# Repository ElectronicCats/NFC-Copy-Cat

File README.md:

# NFC Copy Cat

NFC Copy Cat, manufactured by Electronic Cats, is a small device that combines two powerful cybersecurity tools, NFCopy and MagSpoof. NFCopy works by reading or emulating an NFC card; depending on the necessities of the researcher. On the other hand, MagSpoof can wirelessly emulate/spoof any magnetic stripe card. So using NFC Copy Cat, the user will have a device capable of storing magnetic stripe data or NFC payment data to be replayed later — known in the cybersecurity world as a replay attack. 

To show the capabilities of NFC Copy Cat, the emulation example will use a Visa MSD protocol. So be aware that this type of transaction will not be accepted in some payment systems.

NFC Copy Cat combines a simple user interface that can be programmed using Arduino IDE. Adding a micro USB connection, 3.7V LiPo battery connector, antenna, two programmable buttons, LEDs and a reset button. The most important part, NFC Copy Cat is an open hardware project. So anyone could modify or redesign it on their own.

Devices like NFC Copy Cat are essential for researchers, students, teachers or anyone interested in payment systems. It will help to understand how the payment system works, the communications or the APDU protocol. 

Some of the code examples that will be available introduce different concepts. For example, how to detect a card reader, how to detect an NFC card, how to use MagSpoof using a button as a trigger to spoof, how to use NFC with a button to emulate, how to read a Visa card, how to emulate a Visa MSD card, how to generate challenges to extract card information or how to combine both tools: NFCopy and MagSpoof.

## Features:
- Microcontroller SAMD21 ARM 32-bit Cortex M0
- Memory Flash for support Circuit Python
- Battery Charger 3.7v
- Compatible con Adafruit PN532 breakout
- Compatible con NFC Module V3

### Included Complete Version:
- NFC Copy Cat
- Coil for Magspoof
- NFC Module V3 +Tag 
### Included Single Version:
- NFC Copy Cat
- Coil for Magspoof

## Wiki and Getting Started
[Getting Started in our Wiki](https://github.com/ElectronicCats/NFC-Copy-Cat/wiki)

## Disclaimer
NFC Copy Cat is a wireless penetration testing tool intended solely for use in authorized security audits, where such usage is permitted by applicable laws and regulations. Before utilizing this tool, it is crucial to ensure compliance with all relevant legal requirements and obtain appropriate permissions from the relevant authorities.

It is essential to note that the board does not provide any means or authorization to utilize credit cards or engage in any financial transactions that are not legally authorized. Electronic Cats holds no responsibility for any unauthorized use of the tool or any resulting damages.

## License

Electronic Cats invests time and resources providing this open source design, please support Electronic Cats and open-source hardware by purchasing products from Electronic Cats!

Designed by Electronic Cats.

Firmware released under an GNU AGPL v3.0 license. See the LICENSE file for more information.

Hardware released under an CERN Open Hardware Licence v1.2. See the LICENSE_HARDWARE file for more information.

Electronic Cats is a registered trademark, please do not use if you sell these PCBs.

8 July 2019

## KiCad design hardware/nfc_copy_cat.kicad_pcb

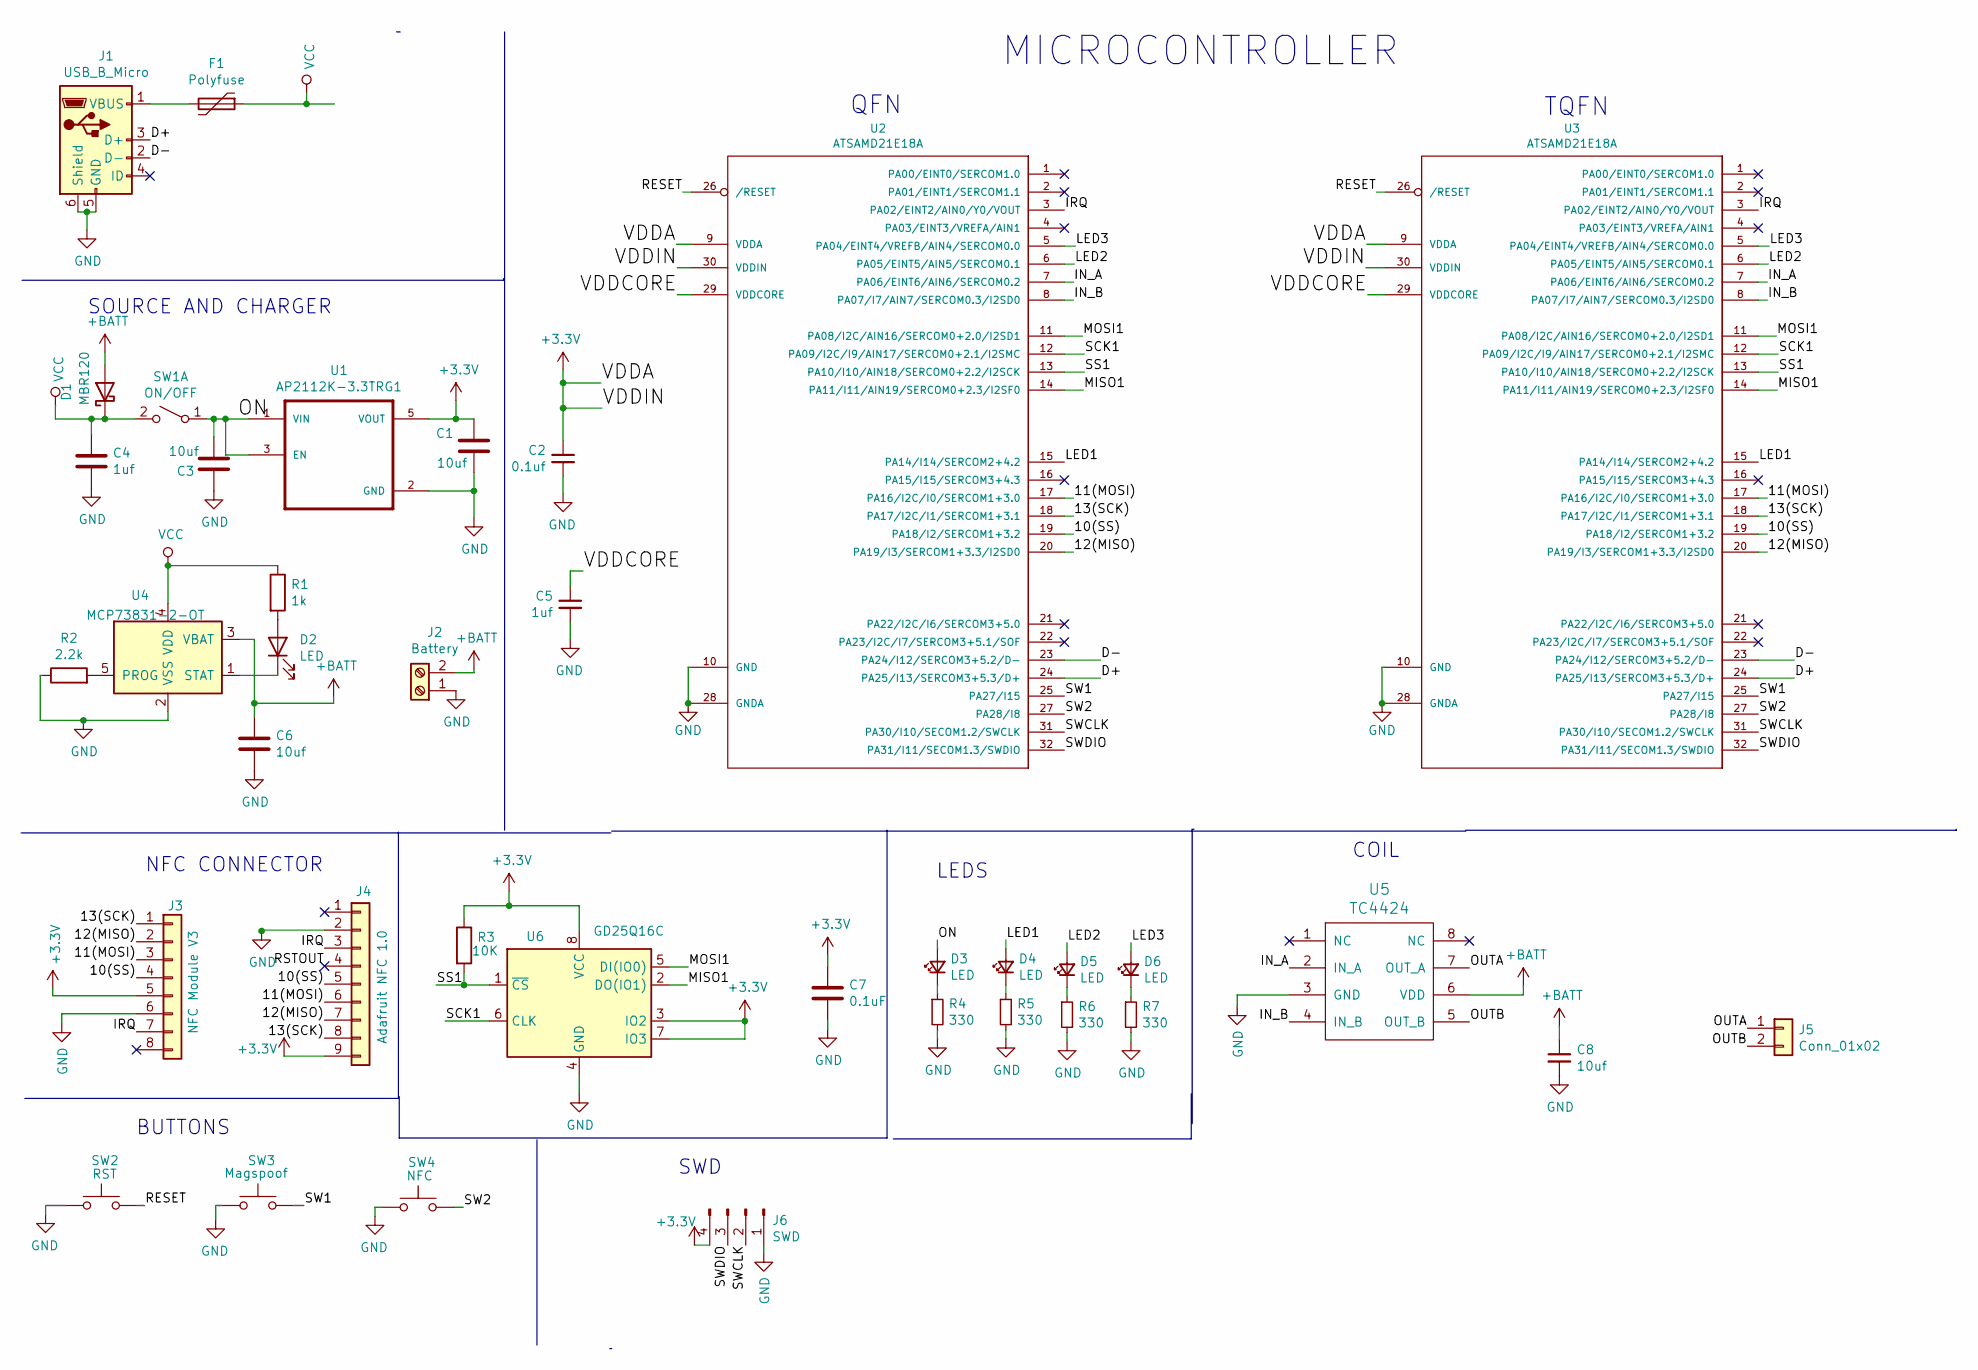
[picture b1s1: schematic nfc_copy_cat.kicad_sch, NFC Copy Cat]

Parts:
C1, C3, C6, C8: 10uf; C_0805_2012Metric_Pad1.15x1.40mm_HandSolder
C2: 0.1uf; C_0805_2012Metric_Pad1.15x1.40mm_HandSolder
C4, C5: 1uf; C_0805_2012Metric_Pad1.15x1.40mm_HandSolder
C7: 0.1uF; C_0805_2012Metric_Pad1.15x1.40mm_HandSolder
D1: MBR120; D_SOD-123
D2, D3, D4, D5, D6: LED; LED_0805_2012Metric_Pad1.15x1.40mm_HandSolder
F1: Polyfuse; Fuse_0805_2012Metric_Pad1.15x1.40mm_HandSolder
J1: USB_B_Micro; U254051N4BH806
J2: Battery; PinHeader_1x02_P2.54mm_Vertical
J3: NFC Module V3; PinHeader_1x08_P2.54mm_Vertical
J4: Adafruit NFC 1.0; PinHeader_1x09_P2.54mm_Vertical
J5: Conn_01x02; PinHeader_1x02_P2.54mm_Vertical
J6: SWD; PinHeader_1x04_P2.54mm_Vertical
R1: 1k; R_0805_2012Metric
R2: 2.2k; R_0805_2012Metric_Pad1.15x1.40mm_HandSolder
R3: 10K; R_0805_2012Metric_Pad1.15x1.40mm_HandSolder
R4: 330; R_0805_2012Metric
R5, R6, R7: 330; R_0805_2012Metric_Pad1.15x1.40mm_HandSolder
SW1: ON/OFF; Micro_interruptor_SPDT
SW2: RST; SW_SPST_TL3342
SW3: Magspoof; SW_SPST_TL3342
SW4: NFC; SW_SPST_TL3342
U1: AP2112K-3.3TRG1; SOT-23-5_HandSoldering
U2: ATSAMD21E18A; QFN-32-1EP_5x5mm_P0.5mm_EP3.6x3.6mm
U3: ATSAMD21E18A; TQFP-32_7x7mm_P0.8mm
U4: MCP73831-2-OT; SOT-23-5
U5: TC4424; SOIC-8_3.9x4.9mm_P1.27mm
U6: GD25Q16C; SOIC-8_5.23x5.23mm_P1.27mm

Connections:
+3V3: C1.1, C2.1, C7.1, J3.5, J4.9, J6.4, R3.1, U1.5 (VOUT), U2.9 (VDDA), U2.30 (VDDIN), U3.9 (VDDA), U3.30 (VDDIN), U6.3 (IO2), U6.7 (IO3), U6.8 (VCC)
+BATT: C6.1, C8.1, D1.2 (A), J2.2, U4.3 (VBAT), U5.6 (VDD)
/10(SS): J3.4, J4.5, U2.19 (PA18/I2/SERCOM1+3.2), U3.19 (PA18/I2/SERCOM1+3.2)
/11(MOSI): J3.3, J4.6, U2.17 (PA16/I2C/I0/SERCOM1+3.0), U3.17 (PA16/I2C/I0/SERCOM1+3.0)
/12(MISO): J3.2, J4.7, U2.20 (PA19/I3/SERCOM1+3.3/I2SD0), U3.20 (PA19/I3/SERCOM1+3.3/I2SD0)
/13(SCK): J3.1, J4.8, U2.18 (PA17/I2C/I1/SERCOM1+3.1), U3.18 (PA17/I2C/I1/SERCOM1+3.1)
/D+: J1.3 (D+), U2.24 (PA25/I13/SERCOM3+5.3/D+), U3.24 (PA25/I13/SERCOM3+5.3/D+)
/D-: J1.2 (D-), U2.23 (PA24/I12/SERCOM3+5.2/D-), U3.23 (PA24/I12/SERCOM3+5.2/D-)
/IN_A: U2.7 (PA06/EINT6/AIN6/SERCOM0.2), U3.7 (PA06/EINT6/AIN6/SERCOM0.2), U5.2 (IN_A)
/IN_B: U2.8 (PA07/I7/AIN7/SERCOM0.3/I2SD0), U3.8 (PA07/I7/AIN7/SERCOM0.3/I2SD0), U5.4 (IN_B)
/IRQ: J3.7, J4.3, U2.3 (PA02/EINT2/AIN0/Y0/VOUT), U3.3 (PA02/EINT2/AIN0/Y0/VOUT)
/LED1: D4.2 (A), U2.15 (PA14/I14/SERCOM2+4.2), U3.15 (PA14/I14/SERCOM2+4.2)
/LED2: D5.2 (A), U2.6 (PA05/EINT5/AIN5/SERCOM0.1), U3.6 (PA05/EINT5/AIN5/SERCOM0.1)
/LED3: D6.2 (A), U2.5 (PA04/EINT4/VREFB/AIN4/SERCOM0.0), U3.5 (PA04/EINT4/VREFB/AIN4/SERCOM0.0)
/MISO1: U2.14 (PA11/I11/AIN19/SERCOM0+2.3/I2SF0), U3.14 (PA11/I11/AIN19/SERCOM0+2.3/I2SF0), U6.2 (DO(IO1))
/MOSI1: U2.11 (PA08/I2C/AIN16/SERCOM0+2.0/I2SD1), U3.11 (PA08/I2C/AIN16/SERCOM0+2.0/I2SD1), U6.5 (DI(IO0))
/OUTA: J5.1, U5.7 (OUT_A)
/OUTB: J5.2, U5.5 (OUT_B)
/RESET: SW2.2, U2.26 (/RESET), U3.26 (/RESET)
/RSTOUT: J4.4
/SCK1: U2.12 (PA09/I2C/I9/AIN17/SERCOM0+2.1/I2SMC), U3.12 (PA09/I2C/I9/AIN17/SERCOM0+2.1/I2SMC), U6.6 (CLK)
/SS1: R3.2, U2.13 (PA10/I10/AIN18/SERCOM0+2.2/I2SCK), U3.13 (PA10/I10/AIN18/SERCOM0+2.2/I2SCK), U6.1 (~CS)
/SW1: SW3.2, U2.25 (PA27/I15), U3.25 (PA27/I15)
/SW2: SW4.2, U2.27 (PA28/I8), U3.27 (PA28/I8)
/SWCLK: J6.2, U2.31 (PA30/I10/SECOM1.2/SWCLK), U3.31 (PA30/I10/SECOM1.2/SWCLK)
/SWDIO: J6.3, U2.32 (PA31/I11/SECOM1.3/SWDIO), U3.32 (PA31/I11/SECOM1.3/SWDIO)
/VDDCORE: C5.1, U2.29 (VDDCORE), U3.29 (VDDCORE)
GND: C1.2, C2.2, C3.2, C4.2, C5.2, C6.2, C7.2, C8.2, J1.5 (GND), J1.6 (Shield), J2.1, J3.6, J4.2, J6.1, R2.1, R4.2, R5.2, R6.2, R7.2, SW2.1, SW3.1, SW4.1, U1.2 (GND), U2.10 (GND), U2.28 (GNDA), U3.10 (GND), U3.28 (GNDA), U4.2 (VSS), U5.3 (GND), U6.4 (GND)
unnamed: D2.1 (K), U4.1 (STAT)
unnamed: D2.2 (A), R1.2
unnamed: D3.1 (K), R4.1
unnamed: D4.1 (K), R5.1
unnamed: D5.1 (K), R6.1
unnamed: D6.1 (K), R7.1
unnamed: F1.2, J1.1 (VBUS)
unnamed: R2.2, U4.5 (PROG)

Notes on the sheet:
QFN
NFC CONNECTOR
LEDS
SWD
TQFN
SOURCE AND CHARGER
COIL
BUTTONS
MICROCONTROLLER

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
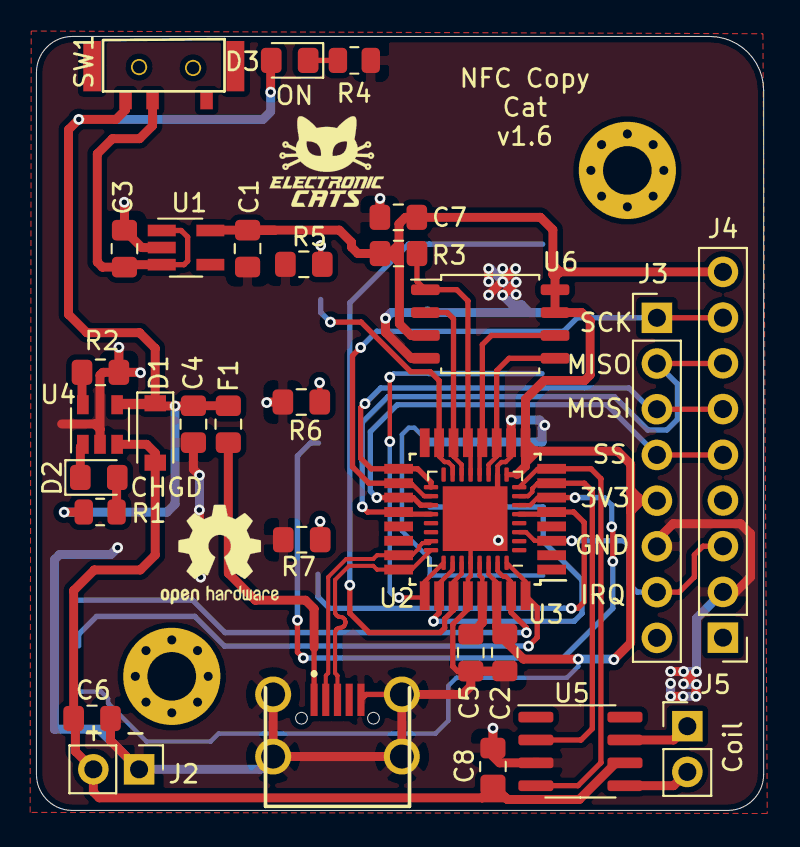
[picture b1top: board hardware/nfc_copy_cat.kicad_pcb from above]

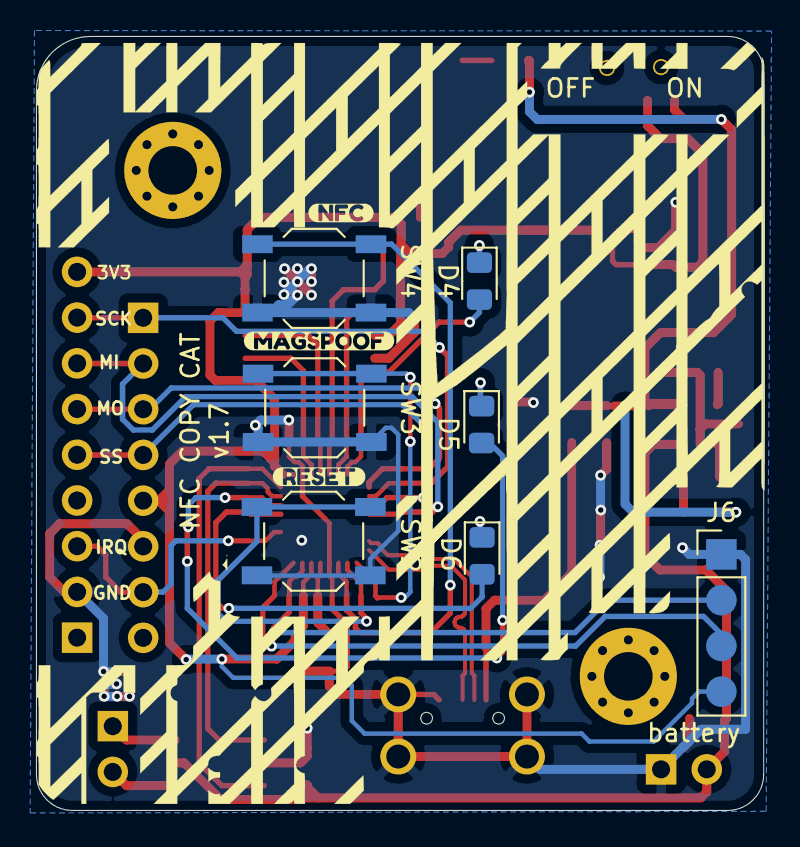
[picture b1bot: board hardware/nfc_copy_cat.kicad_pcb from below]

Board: 2 copper layers, 40.4 x 43.0 mm, 43 parts (10 on the bottom side), 37 nets.

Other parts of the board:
 : MountingHole_2.7mm_M2.5_Pad_Via
 #2: MountingHole_2.7mm_M2.5_Pad_Via
kibuzzard-6234C9E0: G***; kibuzzard-6234C9E0
kibuzzard-6234C9F1: G***; kibuzzard-6234C9F1
kibuzzard-6234C9FD: G***; kibuzzard-6234C9FD

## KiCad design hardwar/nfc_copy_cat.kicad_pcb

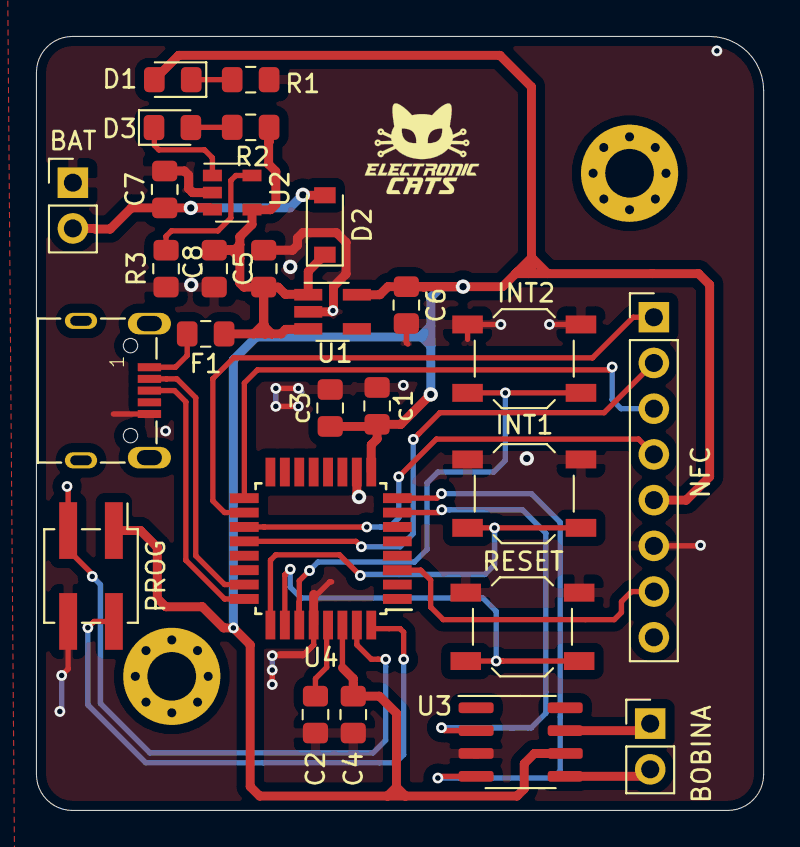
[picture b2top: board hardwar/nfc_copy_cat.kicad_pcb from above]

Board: 2 copper layers, 40.4 x 43.0 mm, 29 parts (0 on the bottom side), 26 nets.

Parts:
 : MountingHole_2.7mm_M2.5_Pad_Via
 #2: MountingHole_2.7mm_M2.5_Pad_Via
BAT: Screw_Terminal_01x02; PinHeader_1x02_P2.54mm_Vertical
BOBINA: Conn_01x02; PinHeader_1x02_P2.54mm_Vertical
C2: 0.1uf; C_0805_2012Metric_Pad1.15x1.40mm_HandSolder
C4: 0.1UF; C_0805_2012Metric_Pad1.15x1.40mm_HandSolder
C5: 1uf; C_0805_2012Metric_Pad1.15x1.40mm_HandSolder
C6, C7, C8: C; C_0805_2012Metric_Pad1.15x1.40mm_HandSolder
D1: LED_Small; LED_0805_2012Metric_Pad1.15x1.40mm_HandSolder
D2: D_Schottky; D_SOD-123
D3: LED; LED_0805_2012Metric_Pad1.15x1.40mm_HandSolder
F1: Polyfuse; Fuse_0805_2012Metric_Pad1.15x1.40mm_HandSolder
INT1, INT2: SW_DPST_x2; SW_SPST_TL3342
J1: USB_B_Micro; 629105150521
NFC: Conn_01x08; PinHeader_1x08_P2.54mm_Vertical
PROG: Conn_02x02_Counter_Clockwise; PinHeader_2x02_P2.54mm_Vertical_SMD
R1: 330; R_0805_2012Metric_Pad1.15x1.40mm_HandSolder
R2, R3: R; R_0805_2012Metric_Pad1.15x1.40mm_HandSolder
RESET: SW_DPST_x2; SW_SPST_TL3342
U1: AP2112K-3.3TRG1; SOT-23-5_HandSoldering
U2: MCP73831-2-OT; SOT-23-5
U3: TC4424; SOIC-8_3.9x4.9mm_P1.27mm
U4: ATSAMD21E18A; TQFP-32_7x7mm_P0.8mm
c1, c3: 0.1uf; C_0805_2012Metric_Pad1.15x1.40mm_HandSolder

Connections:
+3V3: C4.1, C6.1, D1.2, NFC.5, PROG.1, U1.5, U3.6, U4.9, U4.30, c1.1, c3.1
/10(SS): NFC.4, U4.19
/11(MOSI): NFC.3, U4.17
/12(MISO): NFC.2, U4.20
/13(SCK): NFC.1, U4.18
/BAT: BAT.2, C7.1, D2.2, U2.3
/D+: J1.3, U4.24
/D-: J1.2, U4.23
/IN_A: U3.2, U4.7
/IN_B: U3.4, U4.8
/IRQ: NFC.7, U4.3
/OUTA: BOBINA.1, U3.7
/OUTB: BOBINA.2, U3.5
/RESET: RESET.1, U4.26
/SW1: INT1.1, U4.25
/SW2: INT2.1, U4.27
/SWCLK: PROG.3, U4.31
/SWDIO: PROG.2, U4.32
GND: BAT.1, C2.2, C4.2, C5.2, C6.2, C7.2, C8.2, INT1.2, INT2.2, J1.5, NFC.6, PROG.4, R1.2, R3.1, RESET.2, U1.2, U2.2, U3.3, U4.10, U4.28, c1.2, c3.2
unnamed: C2.1, U4.29
unnamed: D1.1, R1.1
unnamed: D3.1, U2.1
unnamed: D3.2, R2.2
unnamed: F1.2, J1.1
unnamed: R3.2, U2.5
VCC: C5.1, C8.1, D2.1, F1.1, R2.1, U1.1, U1.3, U2.4

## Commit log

2019-07-08 primer commit de hardware
2019-07-08 correccion
2019-07-08 Typo fix
2019-07-08 typo xD
2019-07-19 cache rescue
2019-07-22 añadimiento de led
2019-07-30 program
2019-08-02 desplazamiento de botones haca atras
2019-10-30 update schematic
    new connector swd, fix cap vddcore, add leds
2019-10-31 add connector adafruit NFC
2019-12-16 nfc board v3
2019-12-30 rename path
2020-01-02 add labels pinout
2020-01-02 best labels description
2020-01-09 remove c3
2020-01-28 spi flash
2020-01-29 netlist
2020-01-29 fix usb and leds
2020-01-30 routeo charger
2020-02-04 fix push and routeo samd
2020-02-05 TC4424
2020-02-06 change leds and res
2020-02-06 change led 1, res and push
2020-02-07 routeo 3v and samd
2020-02-07 routeo reset and usb
2020-02-07 routeo gnd
2020-02-08 screws
2020-02-08 change screws
2020-02-08 chance c4 eschema
2020-02-08 fix c5, c2 y c1 and sw2
2020-02-08 gnd plane
2020-02-11 change routeo
2020-02-11 fix c5 and sc
2020-02-11 fix logos
2020-02-11 logos ok, and labels
2020-02-12 fix pin
2020-02-13 chance labels
2020-02-13 name
2020-02-20 update silkS
2020-02-20 innecesary files
2020-03-29 Update examples!
2020-04-09 Add Example NFC Visa
2020-04-09 Add Example VISA MSD NFC
2020-04-09 Add new example Check PDOL
2020-04-09 Update example Copy MSD
2020-04-10 add read and replay spoof
2020-04-10 add DISCLAIMER
2020-04-11 update link store
2020-04-15 fix caps and routes
2020-08-29 Create LICENSE_HARDWARE
2020-08-29 Create LICENSE
2021-04-16 fix caps, change SPI flash and LEDs, add ON/OFF
2021-04-16 change serial begin 9600 standard
2021-04-16 update pins SPI Flash OK
2021-04-16 add SPI flash test
2021-04-16 Update standard serial baud
2021-04-21 change battery source driver
2021-04-21 fixDecouplingCapacitors
2021-08-03 updateSchm
2021-08-03 updatingPCB
2021-08-04 NRoutinginProgress
2021-08-04 fixButtonSchm
2021-08-05 addSwitch
2021-08-05 PCBrouted
2021-08-05 addON/OFFLabel
2022-01-11 update kicad 6
2022-03-18 Add labels and change ON
2022-08-23 Update README.md
    wiki and getting started link with image added
2022-09-29 Issue template added
2022-10-17 Typos fixed
2023-06-14 Update Disclaimer
